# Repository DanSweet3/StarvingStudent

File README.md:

# StarvingStudent
Starving Student Tube Headphone Amplifier

Based on the design files available here: http://www.diyforums.org/SSMH/SSMHoverview.php

Configured to use the commonly available 12AU7 tubes instead of the original 19J6 tubes that are now hard to find.

Also added 2 blue LEDs to run from the main 48V DC input. As long as the supply is 350mA+, this should not be an issue. Some people add these across the heater bias instead to be lower power.

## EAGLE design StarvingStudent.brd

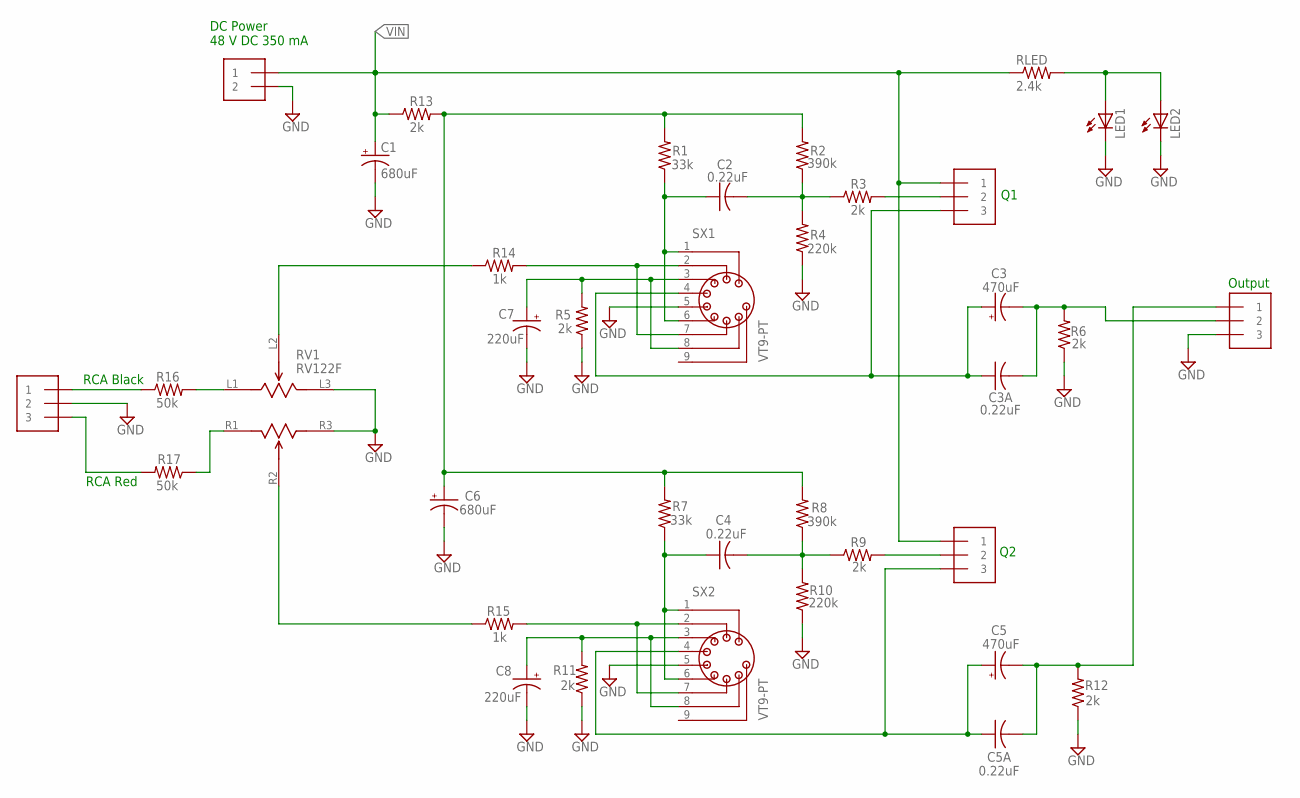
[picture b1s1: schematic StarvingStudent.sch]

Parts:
C1, C6: 680uF; E7,5-18
C2, C3A, C4, C5A: 0.22uF; C150-072X183
C3, C5: 470uF; E5-13
C7, C8: 220uF; E5-13
J1: 1X2-3.5MM
J2, J3, J4, J5: 1X3-3.5MM
LED1, LED2: LED3MM
R1, R7: 33k; 0207/10
R2, R8: 390k; 0207/10
R3, R5, R6, R9, R11, R12, R13: 2k; 0207/10
R4, R10: 220k; 0207/10
R14, R15: 1k; 0207/10
R16, R17: 50k; 0207/10
RLED: 2.4k; 0411/15
RV1: RV122F
SX1, SX2: VT9-PT

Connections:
GND: C1.-, C6.-, C7.-, C8.-, J1.2, J2.2, J5.1 (3), LED1.K (C), LED2.K (C), R4.1, R5.1, R6.1, R10.1, R11.1, R12.1, RV1.L3, RV1.R3, SX1.5, SX2.5
unnamed: J2.3 (1), R16.1
unnamed: J2.1 (3), R17.2
unnamed: C2.1, R1.1, SX1.1, SX1.6
unnamed: C7.+, R5.2, SX1.3, SX1.8
unnamed: R14.2, SX1.2, SX1.7
unnamed: LED1.A, LED2.A, RLED.2
unnamed: C2.2, R2.1, R3.1, R4.2
unnamed: C5.+, C5A.1, J4.1 (3), SX2.4
unnamed: J3.2, R3.2
unnamed: C6.+, R1.2, R2.2, R7.2, R8.2, R13.2
unnamed: C4.1, R7.1, SX2.1, SX2.6
unnamed: C8.+, R11.2, SX2.3, SX2.8
unnamed: R15.2, SX2.2, SX2.7
unnamed: R14.1, RV1.L2
unnamed: C4.2, R8.1, R9.1, R10.2
unnamed: J4.2, R9.2
unnamed: C3.+, C3A.1, J3.1 (3), SX1.4
unnamed: C5.-, C5A.2, J5.3 (1), R12.2
unnamed: R15.1, RV1.R2
unnamed: C3.-, C3A.2, J5.2, R6.2
unnamed: R16.2, RV1.L1
unnamed: R17.1, RV1.R1
VIN: C1.+, J1.1, J3.3 (1), J4.3 (1), R13.1, RLED.1

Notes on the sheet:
RCA Red
RCA Black
Output
DC Power 48 V DC 350 mA

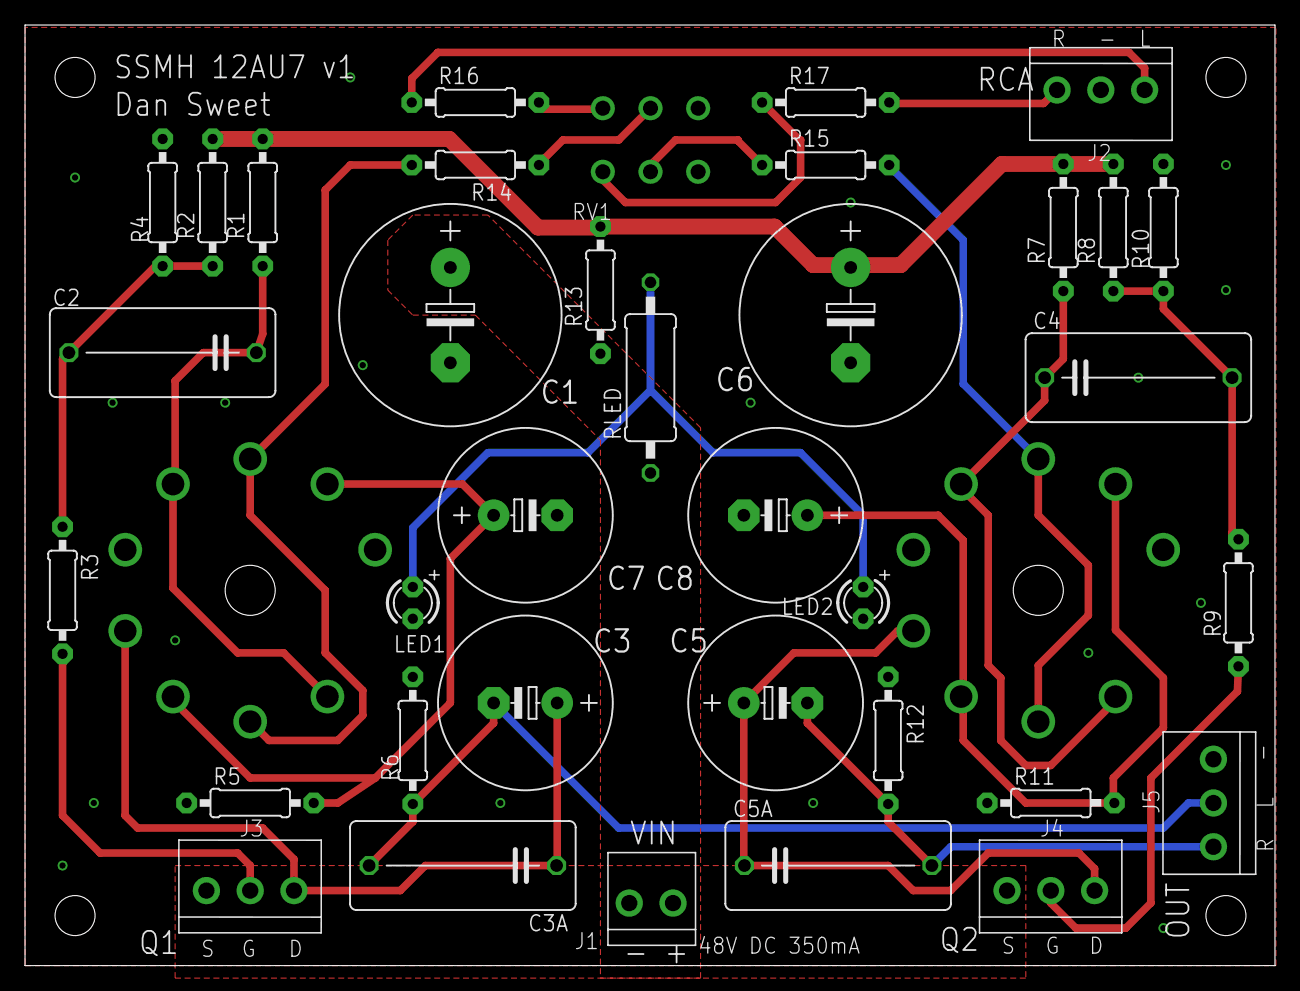
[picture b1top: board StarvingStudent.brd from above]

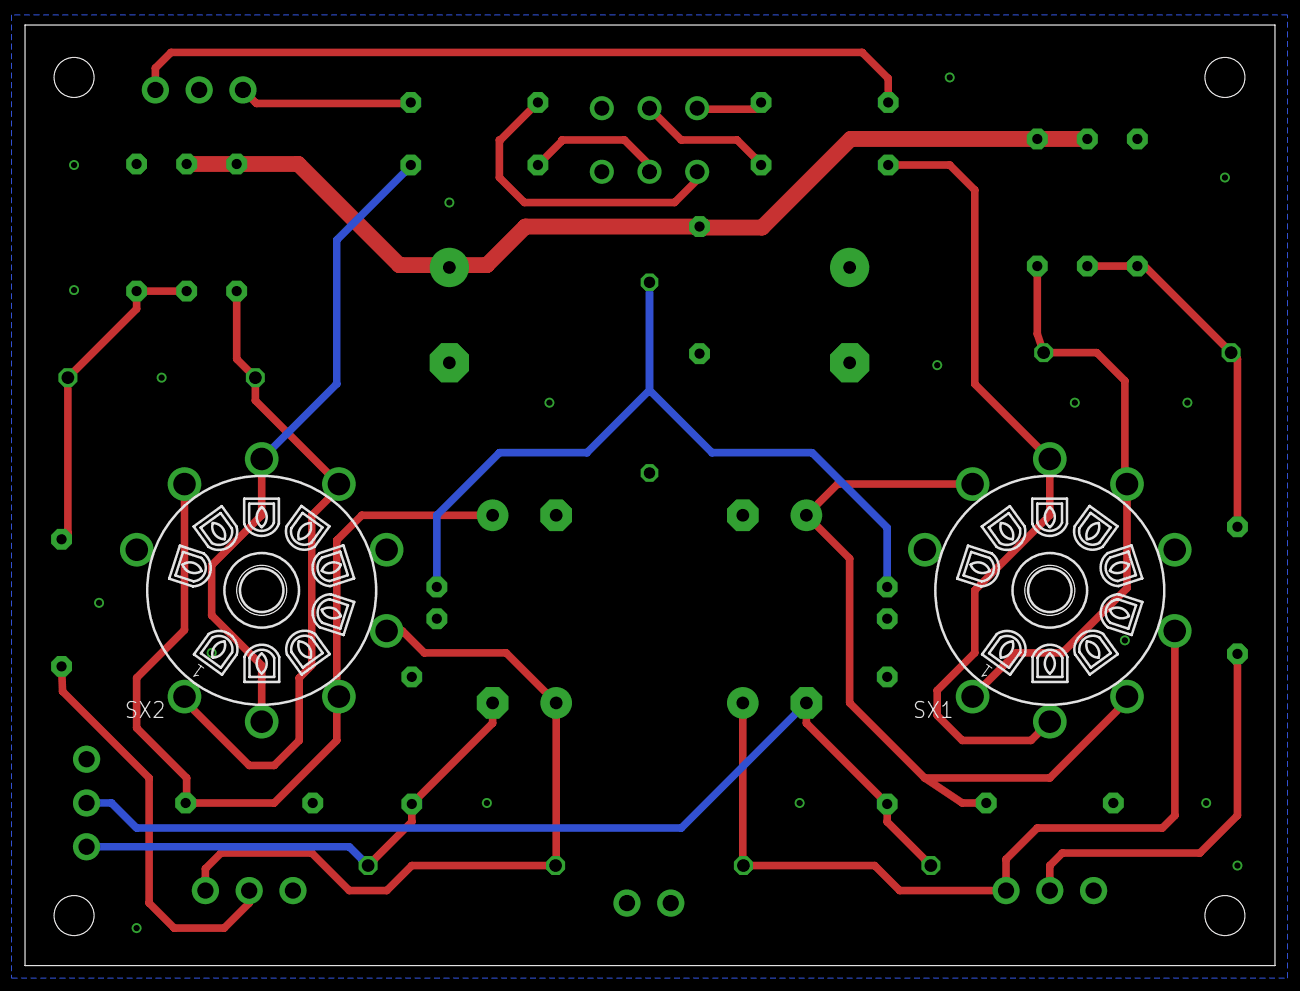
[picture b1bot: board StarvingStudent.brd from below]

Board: 2 copper layers, 99.9 x 75.2 mm, 39 parts (2 on the bottom side), 24 nets.

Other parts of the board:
DRILEGEND: DRILEGEND

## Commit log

2015-12-10 Add board and schematic files.
2015-12-10 Added generated Gerber files and release folder/zip that was sent to Seeed.
2015-12-10 Added drawings document and added drill legend to board file.
2015-12-11 Cleaning up and moving files to try to make everything less messy.
2015-12-11 Added PDF versions of the board and schematic to the doc folder
2015-12-11 Updated readme to give credit to original source.
